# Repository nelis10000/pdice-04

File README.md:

# pdice-04

All design files for the electronic dice building kit for the "Weekend of the Wetenschap 2026" \
\
Microprocessor: PIC12F1572 \
Toolchain: vscode+mplab plugin \
Programmer: PICkit4 or PICkit5

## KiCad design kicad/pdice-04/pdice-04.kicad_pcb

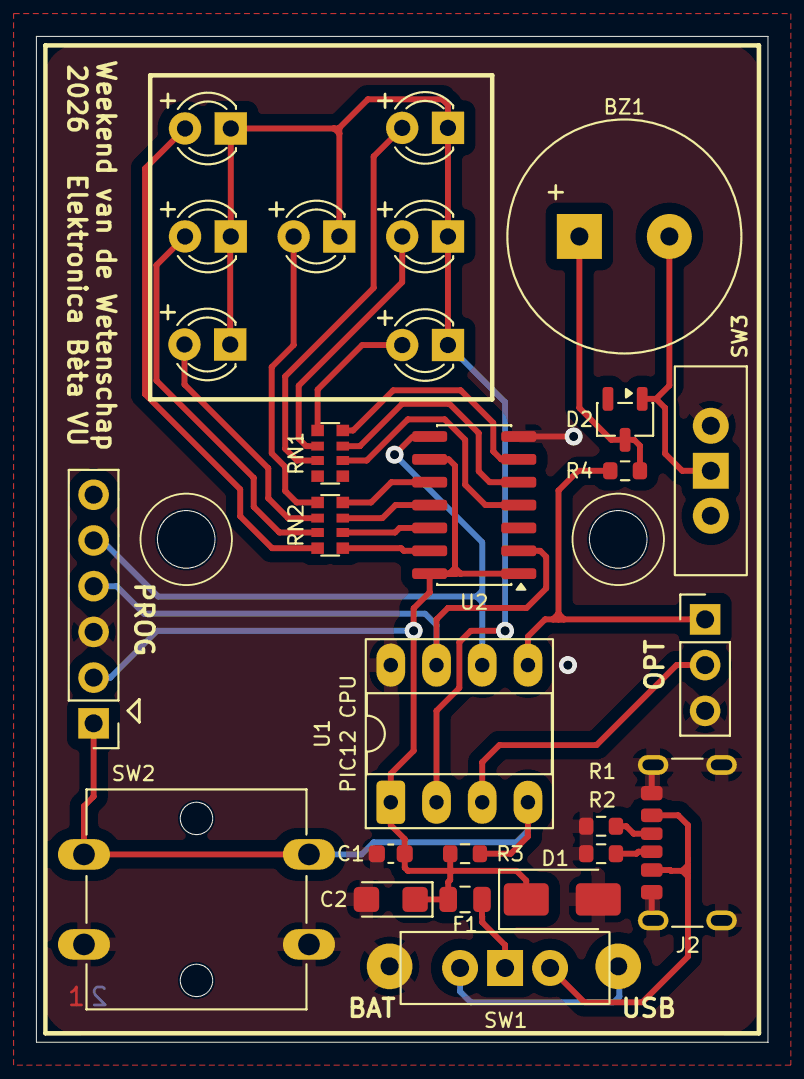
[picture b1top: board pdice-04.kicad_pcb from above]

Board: 2 copper layers, 40.6 x 55.9 mm, 29 parts (1 on the bottom side), 29 nets.

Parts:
BAT1: 3xAAA; Keystone_2479
BZ1: Buzzer; Buzzer_12.5x7.0RM5.0
C1: 100n; C_0603_1608Metric
C2: 47u/6V3/T; CP_EIA-3216-18_Kemet-A
D1: 5V6/1W; D_SMA
D2: BAT54C; SOT-23-3
D3, D4, D5, D6, D7, D8, D9: LED; LED_D3.0mm
F1: 100mA; Fuse_0805_2012Metric
J1: Conn_01x06; PinHeader_1x06_P2.54mm_Vertical
J2: USB_C_Receptacle_PowerOnly_6P; USB_C_Receptacle_GCT_USB4125-xx-x_6P_TopMnt_Horizontal
J3: Conn_01x02; PinHeader_1x03_P2.54mm_Vertical
LOGO1: vukip-bw-01_24.3x25; vukip-bw-01_10.9x11.6
R1, R2: 5k1; R_0603_1608Metric
R3: 47k; R_0603_1608Metric
R4: 0; R_0603_1608Metric
RN1, RN2: R_Pack04; R_Array_Convex_4x0612
SW1, SW3: SW_Slide; SW_Slide-03_E-Switch-EG1218_11.6x4.0x7.4_P2.5mm
SW2: SW_Push; SW_SPST_Omron_B3F-40xx
U1: PIC12F1572; DIP-8_W7.62mm_Socket_LongPads
U2: 74HC164; SO-14_3.9x8.65mm_P1.27mm

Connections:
+3V0: C1.1, C2.1, D1.1 (K), F1.2, J1.2, R3.1, U1.1 (VDD), U2.1 (DSA), U2.9 (~MR), U2.14 (VCC)
/BUZZ: J3.1, R4.1, U1.5 (RA2)
/CLK: J1.5, U1.6 (RA1), U2.8 (CP)
/COM: D3.1 (K), D4.1 (K), D5.1 (K), D6.1 (K), D7.1 (K), D8.1 (K), D9.1 (K), U1.2 (RA5)
/DAT: J1.4, U1.7 (RA0), U2.2 (DSB)
/OPT: J3.2, U1.3 (RA4)
/SW/VPP: J1.1, R3.2, SW2.1, U1.4 (RA3)
/VBAT: BAT1.B+, SW1.1 (A)
/VBUS: J2.A9 (VBUS), J2.B9 (VBUS), SW1.3 (C)
/a: D3.2 (A), RN2.8 (R1.2)
/b: D4.2 (A), RN2.7 (R2.2)
/c: D5.2 (A), RN2.6 (R3.2)
/d: D6.2 (A), RN2.5 (R4.2)
/e: D7.2 (A), RN1.3 (R3.1)
/f: D8.2 (A), RN1.2 (R2.1)
/g: D9.2 (A), RN1.1 (R1.1)
GND: BAT1.B-, C1.2, C2.2, D1.2 (A), J1.3, J2.A12 (GND), J2.B12 (GND), J2.SH (SHIELD), J3.3, R1.2, R2.2, SW2.2, SW3.1 (A), U1.8 (VSS), U2.7 (GND)
unnamed: BZ1.1 (+), D2.3 (K), R4.2
unnamed: BZ1.2 (-), D2.1 (A), SW3.2 (B)
unnamed: J2.A5 (CC1), R2.1
unnamed: J2.B5 (CC2), R1.1
unnamed: RN1.8 (R1.2), U2.6 (Q3)
unnamed: RN1.7 (R2.2), U2.5 (Q2)
unnamed: RN1.6 (R3.2), U2.4 (Q1)
unnamed: RN2.1 (R1.1), U2.13 (Q7)
unnamed: RN2.2 (R2.1), U2.12 (Q6)
unnamed: RN2.3 (R3.1), U2.11 (Q5)
unnamed: RN2.4 (R4.1), U2.10 (Q4)
unnamed: F1.1, SW1.2 (B)

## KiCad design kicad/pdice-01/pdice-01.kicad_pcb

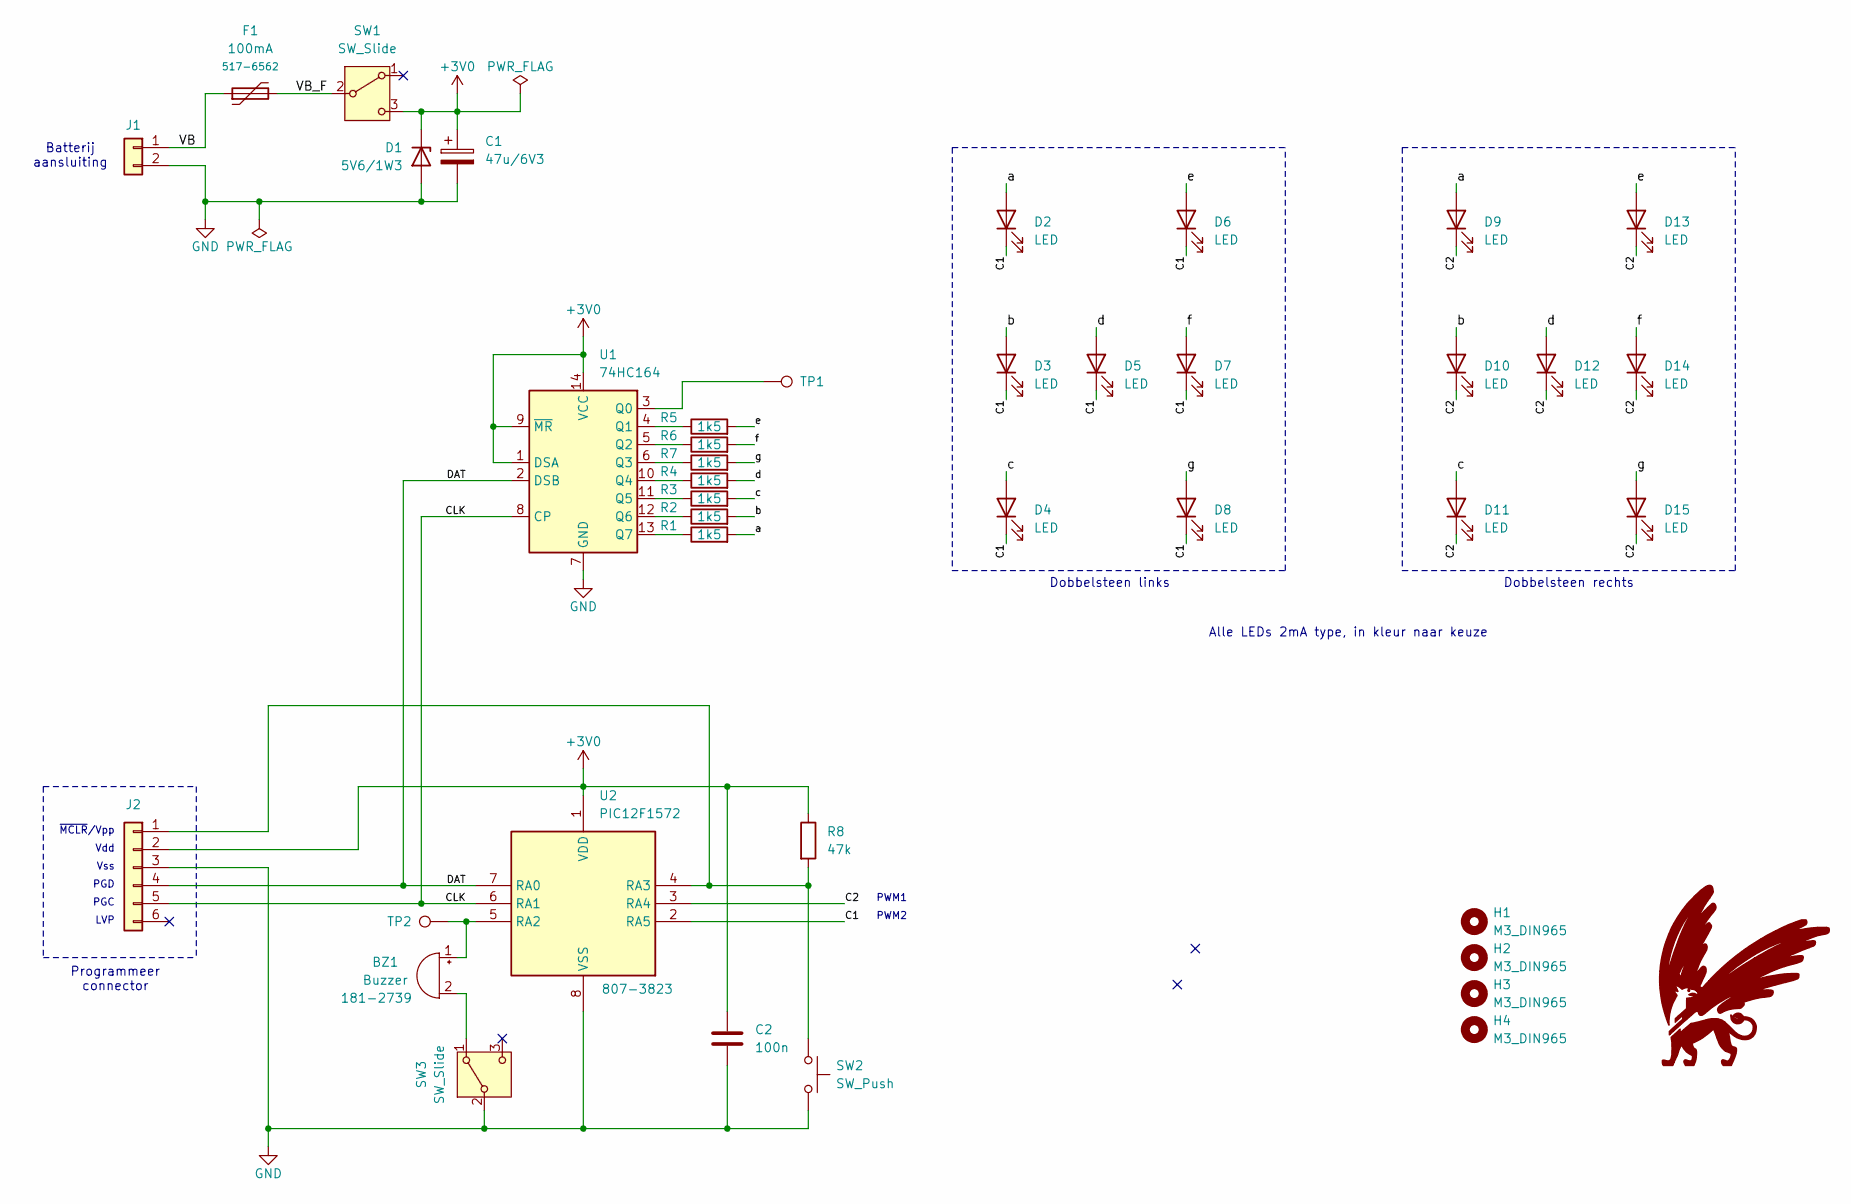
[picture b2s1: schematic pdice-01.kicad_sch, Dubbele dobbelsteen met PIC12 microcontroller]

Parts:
BZ1: Buzzer; Buzzer_15x7.5RM7.6; MPN 181-2739
C1: 47u/6V3; CP_Radial_D6.3mm_P2.50mm
C2: 100n; C_Disc_D5.0mm_W2.5mm_P5.00mm
D1: 5V6/1W3; D_DO-41_SOD81_P7.62mm_Horizontal
D2, D3, D4, D5, D6, D7, D8, D9, D10, D11, D12, D13, D14, D15: LED; LED_D3.0mm
F1: 100mA; C_Disc_D7.5mm_W2.5mm_P5.00mm; MPN RXEF010
H1, H2, H3, H4: M3_DIN965; MountingHole_3.2mm_M3_DIN965
J1: Conn_01x02; SolderWire-0.15sqmm_1x02_P4mm_D0.5mm_OD1.5mm_Relief
J2: Conn_01x06; PinHeader_1x06_P2.54mm_Vertical
LOGO1: vukip-bw-01_24.3x25; vukip-bw-01_10.9x11.6
R1, R2, R3, R4, R5, R6, R7: 1k5; R_Axial_DIN0207_L6.3mm_D2.5mm_P7.62mm_Horizontal
R8: 47k; R_Axial_DIN0207_L6.3mm_D2.5mm_P7.62mm_Horizontal
SW1, SW3: SW_Slide; SW_Slide-03_Wuerth-WS-SLTV_10x2.5x6.4_P2.54mm; MPN WS-SLTV
SW2: SW_Push; SW_SPST_Omron_B3F-40xx
TP1, TP2: TestPoint; TestPoint_THTPad_D1.5mm_Drill0.7mm
U1: 74HC164; DIP-14_W7.62mm_LongPads
U2: PIC12F1572; DIP-8_W7.62mm_LongPads; MPN PIC12F1572-I/P

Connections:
+3V0: C1.1, C2.1, D1.1 (K), J2.2, R8.1, SW1.3 (C), U1.1 (DSA), U1.9 (~MR), U1.14 (VCC), U2.1 (VDD)
/C1: D2.1 (K), D3.1 (K), D4.1 (K), D5.1 (K), D6.1 (K), D7.1 (K), D8.1 (K), U2.2 (RA5)
/C2: D9.1 (K), D10.1 (K), D11.1 (K), D12.1 (K), D13.1 (K), D14.1 (K), D15.1 (K), U2.3 (RA4)
/CLK: J2.5, U1.8 (CP), U2.6 (RA1)
/DAT: J2.4, U1.2 (DSB), U2.7 (RA0)
/VB: F1.1, J1.1
/VB_F: F1.2, SW1.2 (B)
/a: D2.2 (A), D9.2 (A), R1.2
/b: D3.2 (A), D10.2 (A), R2.2
/c: D4.2 (A), D11.2 (A), R3.2
/d: D5.2 (A), D12.2 (A), R4.2
/e: D6.2 (A), D13.2 (A), R5.2
/f: D7.2 (A), D14.2 (A), R6.2
/g: D8.2 (A), D15.2 (A), R7.2
GND: C1.2, C2.2, D1.2 (A), J1.2, J2.3, SW2.2, SW3.2 (B), U1.7 (GND), U2.8 (VSS)
unnamed: BZ1.1 (+), TP2.1 (1_1), U2.5 (RA2)
unnamed: BZ1.2 (-), SW3.1 (A)
unnamed: J2.1, R8.2, SW2.1, U2.4 (RA3)
unnamed: TP1.1 (1_1), U1.3 (Q0)
unnamed: R5.1, U1.4 (Q1)
unnamed: R6.1, U1.5 (Q2)
unnamed: R7.1, U1.6 (Q3)
unnamed: R4.1, U1.10 (Q4)
unnamed: R3.1, U1.11 (Q5)
unnamed: R2.1, U1.12 (Q6)
unnamed: R1.1, U1.13 (Q7)

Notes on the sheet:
Dobbelsteen rechts
PWM2
Vdd
Dobbelsteen links
~{MCLR}/Vpp
Alle LEDs 2mA type, in kleur naar keuze
LVP
Vss
Batterij aansluiting
PWM1
Programmeer connector
PGC
PGD

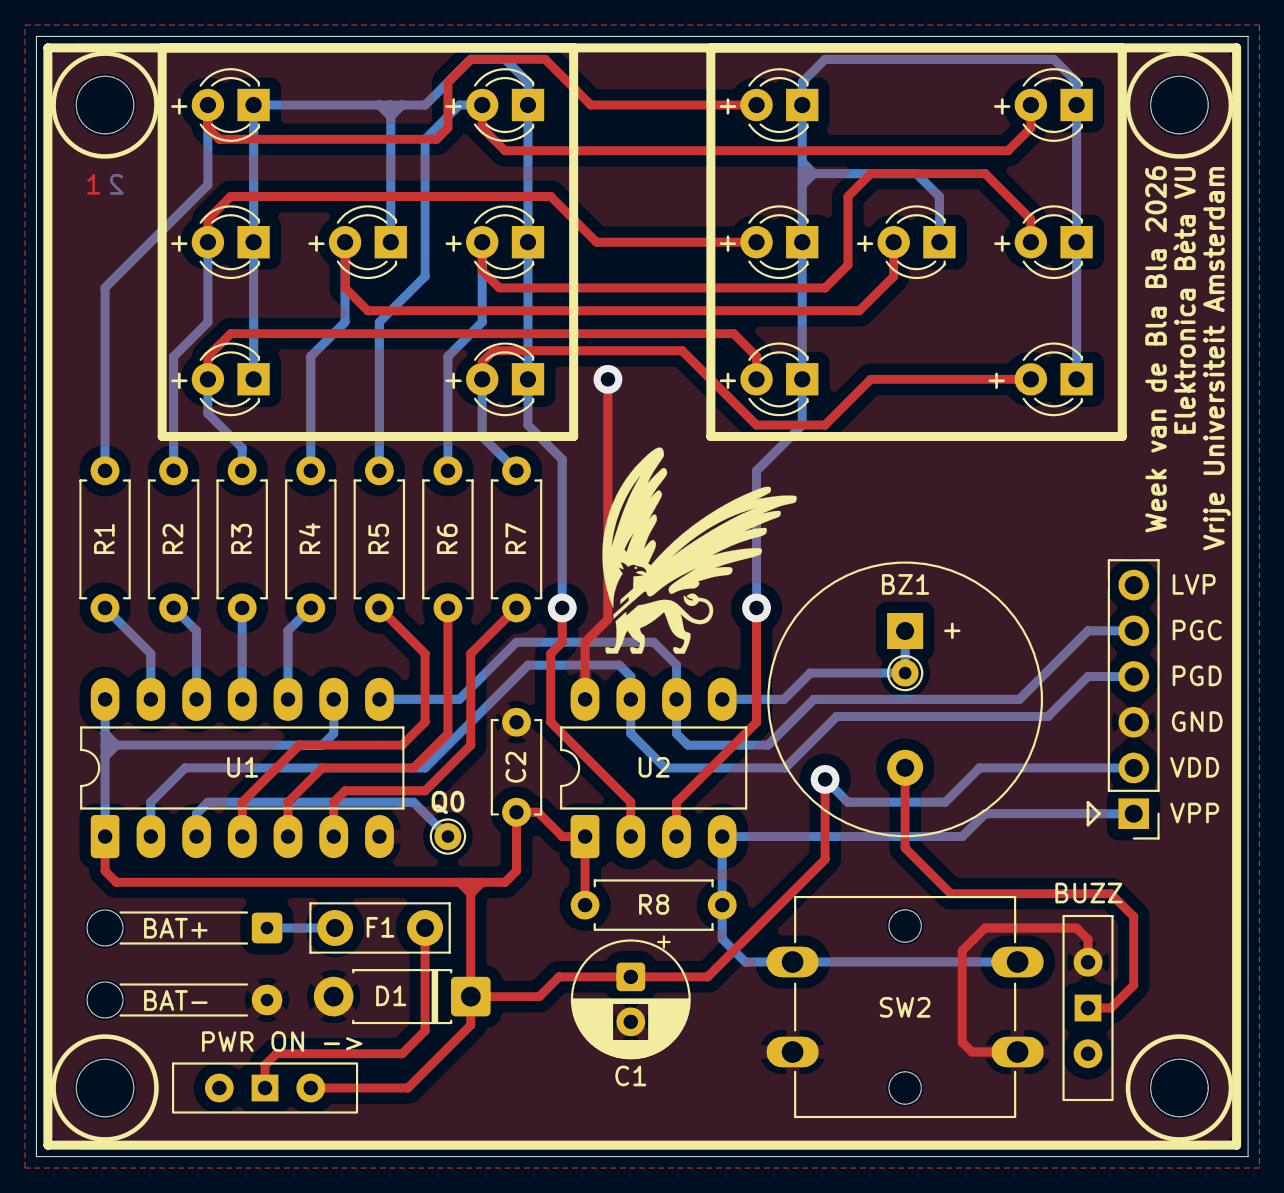
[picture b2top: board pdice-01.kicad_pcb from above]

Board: 2 copper layers, 67.3 x 62.2 mm, 41 parts (0 on the bottom side), 26 nets.

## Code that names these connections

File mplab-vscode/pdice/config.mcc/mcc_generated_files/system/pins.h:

/**
 * Generated Pins header File
 * 
 * @file pins.h
 * 
 * @defgroup  pinsdriver Pins Driver
 * 
 * @brief This is generated driver header for pins. 
 *        This header file provides APIs for all pins selected in the GUI.
 *
 * @version Driver Version  3.0.0
*/

/*
© [2026] Microchip Technology Inc. and its subsidiaries.

    Subject to your compliance with these terms, you may use Microchip 
    software and any derivatives exclusively with Microchip products. 
    You are responsible for complying with 3rd party license terms  
    applicable to your use of 3rd party software (including open source  
    software) that may accompany Microchip software. SOFTWARE IS ?AS IS.? 
    NO WARRANTIES, WHETHER EXPRESS, IMPLIED OR STATUTORY, APPLY TO THIS 
    SOFTWARE, INCLUDING ANY IMPLIED WARRANTIES OF NON-INFRINGEMENT,  
    MERCHANTABILITY, OR FITNESS FOR A PARTICULAR PURPOSE. IN NO EVENT 
    WILL MICROCHIP BE LIABLE FOR ANY INDIRECT, SPECIAL, PUNITIVE, 
    INCIDENTAL OR CONSEQUENTIAL LOSS, DAMAGE, COST OR EXPENSE OF ANY 
    KIND WHATSOEVER RELATED TO THE SOFTWARE, HOWEVER CAUSED, EVEN IF 
    MICROCHIP HAS BEEN ADVISED OF THE POSSIBILITY OR THE DAMAGES ARE 
    FORESEEABLE. TO THE FULLEST EXTENT ALLOWED BY LAW, MICROCHIP?S 
    TOTAL LIABILITY ON ALL CLAIMS RELATED TO THE SOFTWARE WILL NOT 
    EXCEED AMOUNT OF FEES, IF ANY, YOU PAID DIRECTLY TO MICROCHIP FOR 
    THIS SOFTWARE.
*/

#ifndef PINS_H
#define PINS_H

#include <xc.h>

#define INPUT   1
#define OUTPUT  0

#define HIGH    1
#define LOW     0

#define ANALOG      1
#define DIGITAL     0

#define PULL_UP_ENABLED      1
#define PULL_UP_DISABLED     0

// get/set IO_RA0 aliases
#define DAT_TRIS                 TRISAbits.TRISA0
#define DAT_LAT                  LATAbits.LATA0
#define DAT_PORT                 PORTAbits.RA0
#define DAT_WPU                  WPUAbits.WPUA0
#define DAT_OD                   ODCONAbits.ODA0
#define DAT_ANS                  ANSELAbits.ANSA0
#define DAT_SetHigh()            do { LATAbits.LATA0 = 1; } while(0)
#define DAT_SetLow()             do { LATAbits.LATA0 = 0; } while(0)
#define DAT_Toggle()             do { LATAbits.LATA0 = ~LATAbits.LATA0; } while(0)
#define DAT_GetValue()           PORTAbits.RA0
#define DAT_SetDigitalInput()    do { TRISAbits.TRISA0 = 1; } while(0)
#define DAT_SetDigitalOutput()   do { TRISAbits.TRISA0 = 0; } while(0)
#define DAT_SetPullup()          do { WPUAbits.WPUA0 = 1; } while(0)
#define DAT_ResetPullup()        do { WPUAbits.WPUA0 = 0; } while(0)
#define DAT_SetPushPull()        do { ODCONAbits.ODA0 = 0; } while(0)
#define DAT_SetOpenDrain()       do { ODCONAbits.ODA0 = 1; } while(0)
#define DAT_SetAnalogMode()      do { ANSELAbits.ANSA0 = 1; } while(0)
#define DAT_SetDigitalMode()     do { ANSELAbits.ANSA0 = 0; } while(0)
// get/set IO_RA1 aliases
#define CLK_TRIS                 TRISAbits.TRISA1
#define CLK_LAT                  LATAbits.LATA1
#define CLK_PORT                 PORTAbits.RA1
#define CLK_WPU                  WPUAbits.WPUA1
#define CLK_OD                   ODCONAbits.ODA1
#define CLK_ANS                  ANSELAbits.ANSA1
#define CLK_SetHigh()            do { LATAbits.LATA1 = 1; } while(0)
#define CLK_SetLow()             do { LATAbits.LATA1 = 0; } while(0)
#define CLK_Toggle()             do { LATAbits.LATA1 = ~LATAbits.LATA1; } while(0)
#define CLK_GetValue()           PORTAbits.RA1
#define CLK_SetDigitalInput()    do { TRISAbits.TRISA1 = 1; } while(0)
#define CLK_SetDigitalOutput()   do { TRISAbits.TRISA1 = 0; } while(0)
#define CLK_SetPullup()          do { WPUAbits.WPUA1 = 1; } while(0)
#define CLK_ResetPullup()        do { WPUAbits.WPUA1 = 0; } while(0)
#define CLK_SetPushPull()        do { ODCONAbits.ODA1 = 0; } while(0)
#define CLK_SetOpenDrain()       do { ODCONAbits.ODA1 = 1; } while(0)
#define CLK_SetAnalogMode()      do { ANSELAbits.ANSA1 = 1; } while(0)
#define CLK_SetDigitalMode()     do { ANSELAbits.ANSA1 = 0; } while(0)
// get/set IO_RA2 aliases
#define BUZZ_TRIS                 TRISAbits.TRISA2
#define BUZZ_LAT                  LATAbits.LATA2
#define BUZZ_PORT                 PORTAbits.RA2
#define BUZZ_WPU                  WPUAbits.WPUA2
#define BUZZ_OD                   ODCONAbits.ODA2
#define BUZZ_ANS                  ANSELAbits.ANSA2
#define BUZZ_SetHigh()            do { LATAbits.LATA2 = 1; } while(0)
#define BUZZ_SetLow()             do { LATAbits.LATA2 = 0; } while(0)
#define BUZZ_Toggle()             do { LATAbits.LATA2 = ~LATAbits.LATA2; } while(0)
#define BUZZ_GetValue()           PORTAbits.RA2
#define BUZZ_SetDigitalInput()    do { TRISAbits.TRISA2 = 1; } while(0)
#define BUZZ_SetDigitalOutput()   do { TRISAbits.TRISA2 = 0; } while(0)
#define BUZZ_SetPullup()          do { WPUAbits.WPUA2 = 1; } while(0)
#define BUZZ_ResetPullup()        do { WPUAbits.WPUA2 = 0; } while(0)
#define BUZZ_SetPushPull()        do { ODCONAbits.ODA2 = 0; } while(0)
#define BUZZ_SetOpenDrain()       do { ODCONAbits.ODA2 = 1; } while(0)
#define BUZZ_SetAnalogMode()      do { ANSELAbits.ANSA2 = 1; } while(0)
#define BUZZ_SetDigitalMode()     do { ANSELAbits.ANSA2 = 0; } while(0)
// get/set IO_RA3 aliases
#define SWITCH_TRIS                 TRISAbits.TRISA3
#define SWITCH_LAT                  LATAbits.
#define SWITCH_PORT                 PORTAbits.RA3
#define SWITCH_WPU                  WPUAbits.WPUA3
#define SWITCH_OD                   ODCONAbits.
#define SWITCH_ANS                  ANSELAbits.
#define SWITCH_SetHigh()            do { LATAbits. = 1; } while(0)
#define SWITCH_SetLow()             do { LATAbits. = 0; } while(0)
#define SWITCH_Toggle()             do { LATAbits. = ~LATAbits.; } while(0)
#define SWITCH_GetValue()           PORTAbits.RA3
#define SWITCH_SetDigitalInput()    do { TRISAbits.TRISA3 = 1; } while(0)
#define SWITCH_SetDigitalOutput()   do { TRISAbits.TRISA3 = 0; } while(0)
#define SWITCH_SetPullup()          do { WPUAbits.WPUA3 = 1; } while(0)
#define SWITCH_ResetPullup()        do { WPUAbits.WPUA3 = 0; } while(0)
#define SWITCH_SetPushPull()        do { ODCONAbits. = 0; } while(0)
#define SWITCH_SetOpenDrain()       do { ODCONAbits. = 1; } while(0)
#define SWITCH_SetAnalogMode()      do { ANSELAbits. = 1; } while(0)
#define SWITCH_SetDigitalMode()     do { ANSELAbits. = 0; } while(0)
// get/set IO_RA4 aliases
#define OPT_TRIS                 TRISAbits.TRISA4
#define OPT_LAT                  LATAbits.LATA4
#define OPT_PORT                 PORTAbits.RA4
#define OPT_WPU                  WPUAbits.WPUA4
#define OPT_OD                   ODCONAbits.ODA4
#define OPT_ANS                  ANSELAbits.ANSA4
#define OPT_SetHigh()            do { LATAbits.LATA4 = 1; } while(0)
#define OPT_SetLow()             do { LATAbits.LATA4 = 0; } while(0)
#define OPT_Toggle()             do { LATAbits.LATA4 = ~LATAbits.LATA4; } while(0)
#define OPT_GetValue()           PORTAbits.RA4
#define OPT_SetDigitalInput()    do { TRISAbits.TRISA4 = 1; } while(0)
#define OPT_SetDigitalOutput()   do { TRISAbits.TRISA4 = 0; } while(0)
#define OPT_SetPullup()          do { WPUAbits.WPUA4 = 1; } while(0)
#define OPT_ResetPullup()        do { WPUAbits.WPUA4 = 0; } while(0)
#define OPT_SetPushPull()        do { ODCONAbits.ODA4 = 0; } while(0)
#define OPT_SetOpenDrain()       do { ODCONAbits.ODA4 = 1; } while(0)
#define OPT_SetAnalogMode()      do { ANSELAbits.ANSA4 = 1; } while(0)
#define OPT_SetDigitalMode()     do { ANSELAbits.ANSA4 = 0; } while(0)
// get/set IO_RA5 aliases
#define COM_TRIS                 TRISAbits.TRISA5
#define COM_LAT                  LATAbits.LATA5
#define COM_PORT                 PORTAbits.RA5
#define COM_WPU                  WPUAbits.WPUA5
#define COM_OD                   ODCONAbits.ODA5
#define COM_ANS                  ANSELAbits.
#define COM_SetHigh()            do { LATAbits.LATA5 = 1; } while(0)
#define COM_SetLow()             do { LATAbits.LATA5 = 0; } while(0)
#define COM_Toggle()             do { LATAbits.LATA5 = ~LATAbits.LATA5; } while(0)
#define COM_GetValue()           PORTAbits.RA5
#define COM_SetDigitalInput()    do { TRISAbits.TRISA5 = 1; } while(0)
#define COM_SetDigitalOutput()   do { TRISAbits.TRISA5 = 0; } while(0)
#define COM_SetPullup()          do { WPUAbits.WPUA5 = 1; } while(0)
#define COM_ResetPullup()        do { WPUAbits.WPUA5 = 0; } while(0)
#define COM_SetPushPull()        do { ODCONAbits.ODA5 = 0; } while(0)
#define COM_SetOpenDrain()       do { ODCONAbits.ODA5 = 1; } while(0)
#define COM_SetAnalogMode()      do { ANSELAbits. = 1; } while(0)
#define COM_SetDigitalMode()     do { ANSELAbits. = 0; } while(0)
/**
 * @ingroup  pinsdriver
 * @brief GPIO and peripheral I/O initialization
 * @param none
 * @return none
 */
void PIN_MANAGER_Initialize (void);

/**
 * @ingroup  pinsdriver
 * @brief Interrupt on Change Handling routine
 * @param none
 * @return none
 */
void PIN_MANAGER_IOC(void);


#endif // PINS_H
/**
 End of File
*/
